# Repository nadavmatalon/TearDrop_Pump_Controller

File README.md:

#TearDrop Pump Controller

##Table of Contents

* [Screenshots](#screenshots)
* [About the Project](#about-the-project)
* [About the Pump Controller](#about-the-pump-controller)
* [License](#license)

##Screenshots

<table>
	<tr>
		<td align="center" width=25% >
			
		</td>
		<td align="center" width=25% >
			
		</td>
		<td align="center" width=25% >
			
		</td>
		<td align="center" width=25% >
			
		</td>
	</tr>
</table>

##About the Project
 
__TearDrop__ is a custom, open-frame, water-cooled scratch build I’ve been 
working on as part of the SnowCrash initiative.

The __SnowCrash__ initiative aims at designing and building end-to-end customized 
personal computers, addressing unique functional requirements – from developing 
the software control applications, to hardware configuration and case modding. 
As part of the initiative's research phase, the TearDrop customized computer 
prototype has been developed.

The underlying motivation for this specifc project was to research, design, 
prototype and finally create everything that's needed for a fully-customized 
desktop computer.

In this context, I’ve learned to program micro-controllers, design, prototype 
and build electronic circuit boards, make CNC cutting templates, interface with 
various kinds of hardware, write front-end applications, and lots more.

This project also helped me to become proficient in multiple software tools, including: 
[Google Sketchup](http://www.sketchup.com/), 
[Arduino IDE](http://www.arduino.cc/), [Processing 2.0](http://processing.org/), 
[CadSoft Eagle](http://www.cadsoftusa.com/download-eagle/freeware/), 
and [Inkscape](http://www.inkscape.org/en/).
 
The __project-log__ of this build (which I haven't had time to update recently, but 
does include loads of cool pictures :-), can be found 
at [bit-tech](http://forums.bit-tech.net/showthread.php?t=234218).

##About the Pump Controller

This repo contains the custom Pump Controller I’ve designed and built 
to control __TearDrop__’s dual-pump cooling system.

This repo contains the following files:

* __arduino__

    The source code for the ATmega328P that runs the Pump Controller 

    The file can can be directly accessed by clicking this link:

    * [Pump Controller](arduino/TearDrop_Pump_Controller/TearDrop_Pump_Controller.ino)

	The source code requires three supporting open-source [Arduino](http://www.arduino.cc/) libraries.

	For convenience, these libraries are inlcuded here in their own sub-folder.

	Credit goes to:

	[PinChangeInt](http://playground.arduino.cc/Main/PinChangeInt)

	[OneWire](https://github.com/ntruchsess/arduino-OneWire/tree/master)

	[WSWire](https://github.com/steamfire/WSWireLib)

* __eagle__

    This folder contains the complete hardware schematics & PCB design of the Pump Controller.

    __Please do not click on the files in this sub-folder as they are in foramts that 
    are incompatible with Github's hosting server__.

    However, the files can be downloaded and run as usual with [CadSoft](http://www.cadsoftusa.com/?language=en)'s 
    free version of [Eagle](http://www.cadsoftusa.com/download-eagle/freeware/).

* __parts__

	A speadsheet with all information about the parts used for building the Pump Controller.

	__The file in this sub-folder is also in a foramt that's incompatible with Github's hosting server__.

    However, it can be downloaded and run as usual with any spreadsheet editing software.

##  License

<p>Released under the <a href="http://www.opensource.org/licenses/MIT">MIT license</a>.</p>

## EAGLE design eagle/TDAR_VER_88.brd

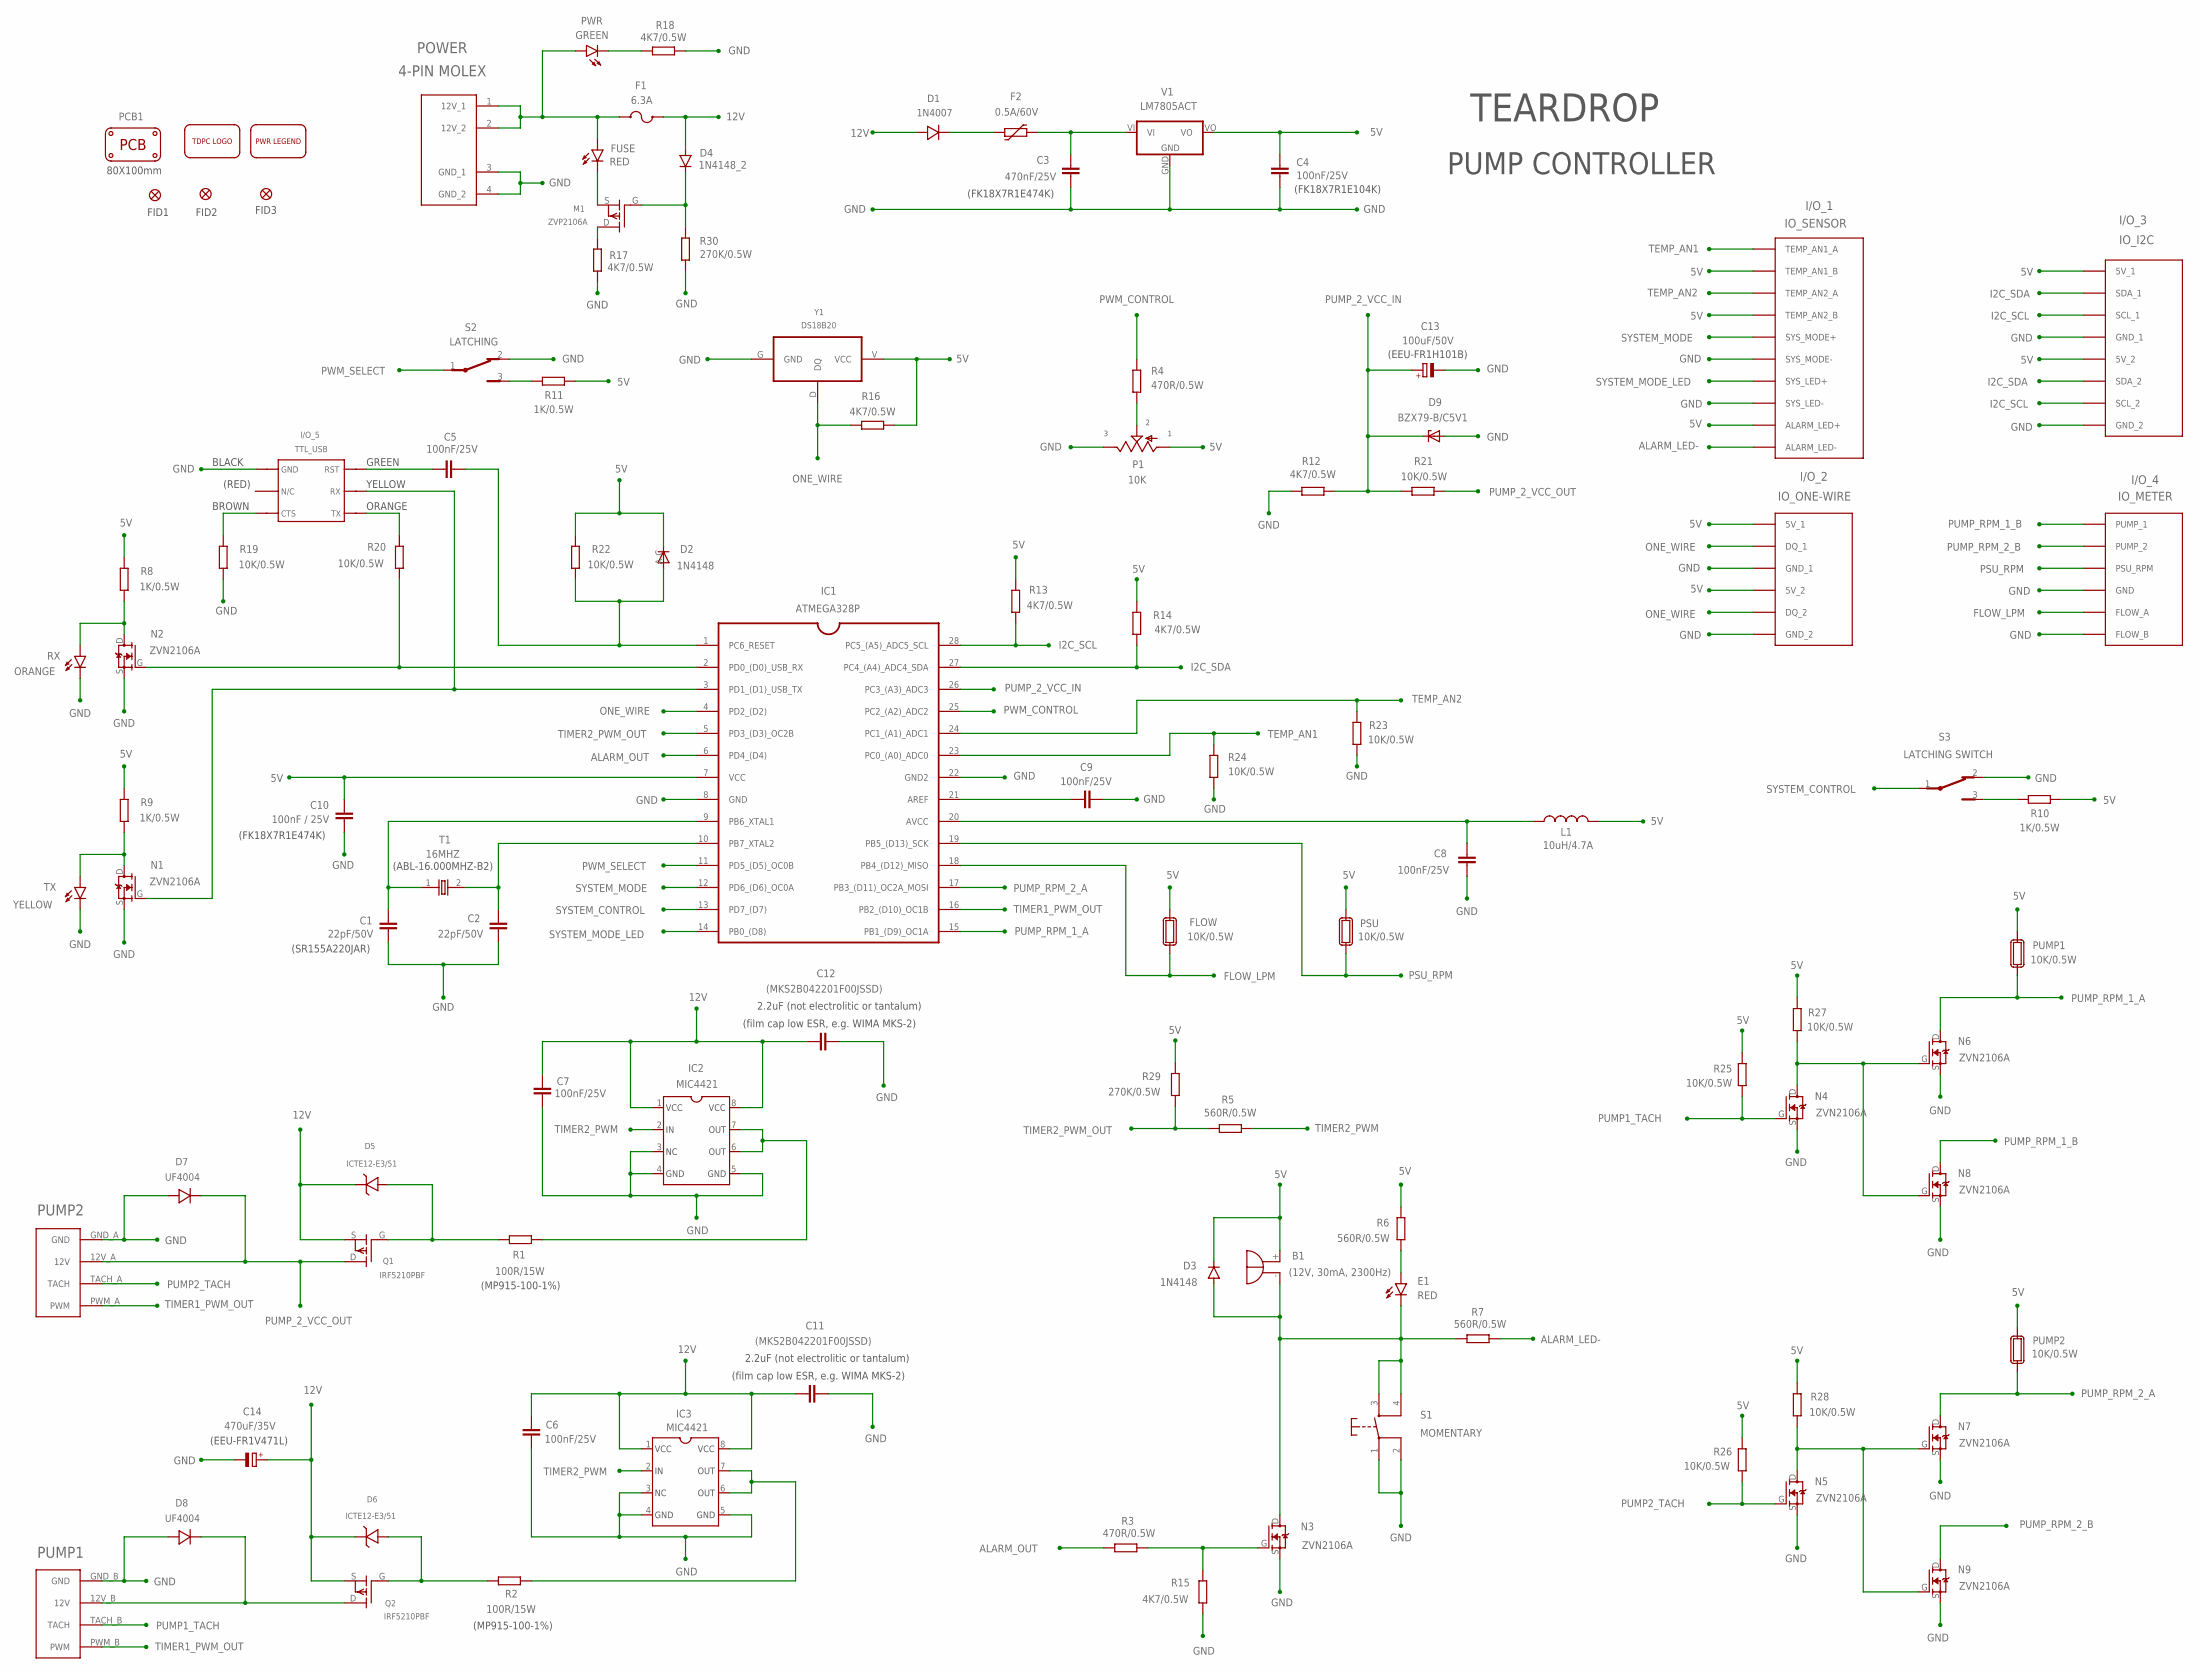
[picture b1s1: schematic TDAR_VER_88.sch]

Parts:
B1: (12V, 30mA, 2300Hz); F/TMB
C1: 22pF/50V; MLCC_CERAMIC_12
C2: 22pF/50V; MLCC_CERAMIC_11
C3: 470nF/25V; MLCC_CERAMIC_8
C4, C5, C6, C7: 100nF/25V; MLCC_CERAMIC
C8, C9: 100nF/25V; MLCC_CERAMIC_7
C10: 100nF / 25V; MLCC_CERAMIC_6
C11, C12: (MKS2B042201F00JSSD); WIMA_CAPACITOR
C13: 100uF/50V; E5-10,5
C14: 470uF/35V; E5-10,5
D1: 1N4007; UF4004
D2: 1N4148; DO35-7
D3: 1N4148
D4: 1N4148_2
D5, D6: ICTE12-E3/51; TVS_DIODE
D7, D8: UF4004; UF4004_2
D9: BZX79-B/C5V1; DO34Z7
E1: RED; LED_5_HORIZONTAL
F1: 6.3A; FUSE_GLASS
F2: 0.5A/60V; PTC
FID1, FID2, FID3: FIDUCIAL1X2; FIDUCIAL-1X2
FLOW: 10K/0.5W; RESISTOR_SOCKET_TOP
FUSE: RED; LED_1.8_LEFT
I/O_1: IO_SENSOR; IO_GENERAL_4
I/O_2: IO_ONE-WIRE; I0_ONE-WIRE
I/O_3: IO_I2C
I/O_4: IO_METER; IO_SENSOR_4
I/O_5: TTL_USB; TTL_USB_7
IC1: ATMEGA328P
IC2, IC3: MIC4421; TC4420
L1: 10uH/4.7A; IRF24
M1: ZVP2106A
N1, N2, N3, N4, N5, N6, N7, N8, N9: ZVN2106A
P1: 10K; POTENTIMETER_SQUARE
PCB1: 80X100mm; DP10080_V1
POWER: 4-PIN MOLEX; MOLEX_4PIN_2
PSU: 10K/0.5W; RESISTOR_SOCKET_TOP
PUMP1, PUMP2: 10K/0.5W; RESISTOR_SOCKET_TOP
PUMP_2: PUMP2; MOLEX_POWER_8_PIN_HORIZONTAL_2
PWR: GREEN; LED_1.8_LEFT
Q1, Q2: IRF5210PBF; IRF5210
R1, R2: 100R/15W; V234/12
R3, R4: 470R/0.5W; 0204/5
R5, R6, R7: 560R/0.5W; 0204/5
R8, R9, R10, R11: 1K/0.5W; 0204/5
R12, R13, R14, R15, R16, R17, R18: 4K7/0.5W; 0204/5
R19, R20, R21, R22, R23, R24, R25, R26, R27, R28: 10K/0.5W; 0204/5
R29, R30: 270K/0.5W; 0204/5
RX: ORANGE; LED_1.8_RIGHT
S1: MOMENTARY; MOM_SWITCH_6.0
S2: LATCHING; SLIDING_SWITCH_5
S3: LATCHING SWITCH; SLIDING_SWITCH_4
T1: 16MHZ; CRYSTAL_16MHZ
TX: YELLOW; LED_1.8_RIGHT
U$1: TDPC_LOGO
U$2: MOLEX_4PIN_LEGEND
V1: LM7805ACT; LM7805
Y1: DS18B20

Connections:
5V: B1.+, C4.2, C10.1, D2.C, D3.C, FLOW.1, I/O_1.5V_1 (TEMP_AN1_B), I/O_1.5V_2 (TEMP_AN2_B), I/O_1.ALARM_LED+, I/O_2.5V_1, I/O_2.5V_2, I/O_3.5V_1, I/O_3.5V_2, IC1.7 (VCC), L1.2, P1.1 (A), PSU.1, PUMP1.1, PUMP2.1, R6.1, R8.1, R9.1, R10.2, R11.2, R13.2, R14.1, R16.2, R22.1, R25.1, R26.1, R27.1, R28.2, R29.1, V1.VO, Y1.V (VCC)
12V: C6.2, C7.2, C11.1, C12.1, C14.+, D1.A, D4.A, D5.C, D6.C, F1.2, IC2.1, IC2.8, IC3.1, IC3.8, Q1.S, Q2.S
ALARM_LED-: I/O_1.ALARM_LED-, R7.2
ALARM_OUT: IC1.6 (PD4_(D4)), R3.2
CRYSTAL_A: C1.1, IC1.9 (PB6_XTAL1), T1.1
CRYSTAL_B: C2.1, IC1.10 (PB7_XTAL2), T1.2
D4: D5.A, Q1.G, R1.1
FLOW_LPM: FLOW.2, I/O_4.FLOW_A, IC1.18 (PB4_(D12)_MISO)
GND: C1.2, C2.2, C3.2, C4.1, C6.1, C7.1, C8.2, C9.2, C10.2, C11.2, C12.2, C13.-, C14.-, D7.A, D8.A, D9.A, I/O_1.SYSTEM_LED- (SYS_LED-), I/O_1.SYSTEM_MODE- (SYS_MODE-), I/O_2.GND_1, I/O_2.GND_2, I/O_3.GND_1, I/O_3.GND_2, I/O_4.FLOW_B, I/O_4.GND, I/O_5.GND, IC1.8 (GND), IC1.22 (GND2), IC2.3, IC2.4, IC2.5, IC3.3, IC3.4, IC3.5, N1.S, N2.S, N3.S, N4.S, N5.S, N6.S, N7.S, N8.S, N9.S, P1.3 (E), POWER.3 (GND_1), POWER.4 (GND_2), PUMP_2.GND_A (GND), PUMP_2.GND_B (GND), R12.1, R15.1, R17.2, R18.1, R19.2, R23.1, R24.2, R30.2, RX.K (C), S1.1, S1.2, S2.2, S3.2, TX.K (C), V1.GND, Y1.G (GND)
I2C_SCL: I/O_3.SCL_1, I/O_3.SCL_2, IC1.28 (PC5_(A5)_ADC5_SCL), R13.1
I2C_SDA: I/O_3.SDA_1, I/O_3.SDA_2, IC1.27 (PC4_(A4)_ADC4_SDA), R14.2
unnamed: R11.1, S2.3
unnamed: D4.C, M1.G, R30.1
unnamed: C8.1, IC1.20 (AVCC), L1.1
unnamed: PWR.K (C), R18.2
unnamed: P1.2 (S), R4.1
unnamed: IC2.6, IC2.7, R1.2
unnamed: D6.A, Q2.G, R2.1
unnamed: IC3.6, IC3.7, R2.2
unnamed: FUSE.K (C), M1.S
unnamed: N4.D, N6.G, N8.G, R27.2
unnamed: C9.1, IC1.21 (AREF)
unnamed: N3.G, R3.1, R15.2
unnamed: R10.1, S3.3
unnamed: D1.C, F2.1
unnamed: N1.D, R9.2, TX.A
unnamed: N2.D, R8.2, RX.A
unnamed: M1.D, R17.1
unnamed: E1.A, R6.2
unnamed: N5.D, N7.G, N9.G, R28.1
unnamed: B1.-, D3.A, E1.K (C), N3.D, R7.1, S1.3, S1.4
ONE_WIRE: I/O_2.DQ_1, I/O_2.DQ_2, IC1.4 (PD2_(D2)), R16.1, Y1.D (DQ)
POST_FUSE: C3.1, F2.2, V1.VI
PSU_RPM: I/O_4.PSU (PSU_RPM), IC1.19 (PB5_(D13)_SCK), PSU.2
PUMP1_TACH: N4.G, PUMP_2.TACH_B (TACH), R25.2
PUMP2_TACH: N5.G, PUMP_2.TACH_A (TACH), R26.2
PUMP_1_VCC_OUT: D8.C, PUMP_2.12V_B (12V), Q2.D
PUMP_2_VCC_IN: C13.+, D9.C, IC1.26 (PC3_(A3)_ADC3), R12.2, R21.1
PUMP_2_VCC_OUT: D7.C, PUMP_2.12V_A (12V), Q1.D, R21.2
PUMP_RPM_1_A: IC1.15 (PB1_(D9)_OC1A), N6.D, PUMP1.2
PUMP_RPM_1_B: I/O_4.PUMP_1, N8.D
PUMP_RPM_2_A: IC1.17 (PB3_(D11)_OC2A_MOSI), N7.D, PUMP2.2
PUMP_RPM_2_B: I/O_4.PUMP_2, N9.D
PWM_CONTROL: IC1.25 (PC2_(A2)_ADC2), R4.2
PWM_SELECT: IC1.11 (PD5_(D5)_OC0B), S2.1
PWR_IN: F1.1, FUSE.A, POWER.1 (12V_1), POWER.2 (12V_2), PWR.A
RESET: C5.1, D2.A, IC1.1 (PC6_RESET), R22.2
SYSTEM_CONTROL: IC1.13 (PD7_(D7)), S3.1
SYSTEM_MODE: I/O_1.SYSTEM_MODE+ (SYS_MODE+), IC1.12 (PD6_(D6)_OC0A)
SYSTEM_MODE_LED: I/O_1.SYSTEM_LED+ (SYS_LED+), IC1.14 (PB0_(D8))
TEMP_AN1: I/O_1.TEMP_AN1 (TEMP_AN1_A), IC1.23 (PC0_(A0)_ADC0), R24.1
TEMP_AN2: I/O_1.TEMP_AN2 (TEMP_AN2_A), IC1.24 (PC1_(A1)_ADC1), R23.2
TIMER1_PWM_OUT: IC1.16 (PB2_(D10)_OC1B), PUMP_2.PWM_A (PWM), PUMP_2.PWM_B (PWM)
TIMER2_PWM: IC2.2, IC3.2, R5.2
TIMER2_PWM_OUT: IC1.5 (PD3_(D3)_OC2B), R5.1, R29.2
USB_CTS: I/O_5.CTS, R19.1
USB_RESET_2: C5.2, I/O_5.RST
USB_RX: IC1.2 (PD0_(D0)_USB_RX), N2.G, R20.2
USB_RX_2: I/O_5.TX, R20.1
USB_TX: I/O_5.RX, IC1.3 (PD1_(D1)_USB_TX), N1.G

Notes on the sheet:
FID1
FID2
FID3
(film cap low ESR, e.g. WIMA MKS-2)
TEARDROP
GREEN
YELLOW
ORANGE
BROWN
BLACK
(RED)
2.2uF (not electrolitic or tantalum)
(FK18X7R1E104K)
(FK18X7R1E474K)
(SR155A220JAR)
(EEU-FR1V471L)
(EEU-FR1H101B)
(MP915-100-1%)
PUMP1
PUMP CONTROLLER
(ABL-16.000MHZ-B2)

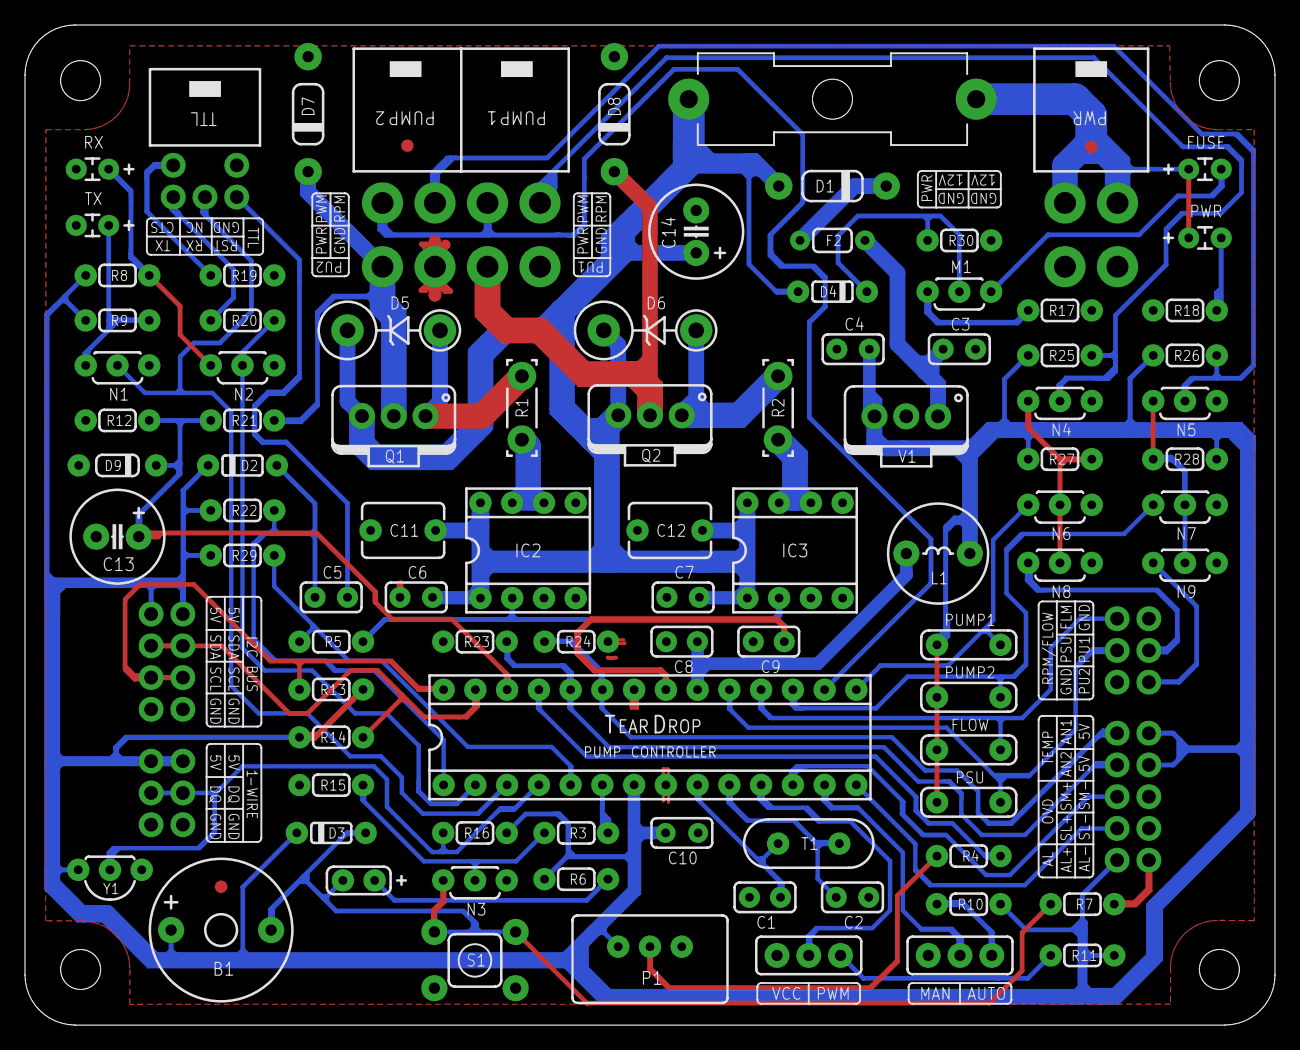
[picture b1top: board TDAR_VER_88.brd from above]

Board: 2 copper layers, 100.0 x 80.0 mm, 101 parts (0 on the bottom side), 60 nets.

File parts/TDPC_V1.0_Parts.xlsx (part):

| TEARDROP
 | NAME | TYPE | VALUE / RATING | PACKAGE / DIMENSIONS | NUMBER | MANUFACTURER | MPN | SOURCE | DATASHEET | ACTUAL | ACTUAL | MINIMUM | ACTUAL | MINIMUM | MINIMUM | ACTUAL | MINIMUM | MINIMUM | MINIMUM
 |  |  |  | (mm) | OF |  |  |  | LEAD | LEAD | LEAD | HOLE | HOLE | ANNULAR RING | PAD | PAD | HOLE | PAD | PAD
 |  |  |  |  | UNITS |  |  |  | DIAMETER | DIAMETER | DIAMETER | DIAMETER | DIAMETER | SIZE | DIAMETER | DIAMETER | DIAMETER | DIAMETER | DIAMETER
 |  |  |  |  |  |  |  |  | (mm) | (wide side) | (narrow side) | (mm) | (mm) | (mm) | (mm) | (mm) | CHECK | CHECK (1) | CHECK (2)
 | PWR, PUMP1, PUMP2 | 4P (2x2) POWER SOCKET (FEMALE) | 10A | KK, HORIZONTAL | 3 | MOLEX | MB-4PIN-SB | modDIY (MB-4PIN-SB) | ─ | 1.2 | 1.2 | 1.454 | 1.75 | 0.2 | 2.25 | 3.3 | 1.35 | 0.14999999999999991 | 1.0499999999999998
 | PWR, PUMP1, PUMP2 | 4P (2x2) POWER CONNECTOR (MALE) | 10A | KK, HORIZONTAL | 3 | MOLEX | MB-4PIN-F | modDIY (MB-4PIN-F) | ─ | ─ | ─ | ─ | ─ | ─ | ─ | ─ | ─ | ─ | ─
 | USB-TTL | 6P (2x3) SOCKET (FEMALE) | RIGHT ANGLE, 2.54 |  | 1 | MOLEX | 90130-3206 | eBay (350819406809) |  |  |  | 0.254 |  | 0.2 | 0.5 | 1.7 | -0.4 | 1.7 | 1.2
 | USB-TTL | 6P (2x3) CONNECTOR (MALE) | ─ | ─ | 1 | MOLEX | 90142-0006 | eBay (111189947049) | ─ | ─ | ─ | ─ | ─ | ─ | ─ | ─ | ─ | ─ | ─
 | USB-TTL | CONNECTOR CRIMPS | ─ | ─ | 6 | MOLEX | 90119-2120 | eBay (111189965216) | ─ | ─ | ─ | ─ | ─ | ─ | ─ | ─ | ─ | ─ | ─
 | I/O | RIGHT-ANGLE MALE HEADERS | 2x3, 2x4, 2x5 | DUAL ROW, 2.54 | 3 | UNKOWN | UNKNOWN | eBay (321027689319) | ─ | 0.7 | 0.7 | 0.95399999999999996 | 1.1000000000000001 | 0.2 | 1.6 | 2 | 0.70000000000000007 | 1.9999999999999796E-2 | 0.39999999999999991
 | IC1 | ATMEGA328P | ─ | DIP-28 | 1 | ATMEL | ATMEGA328P | eBay(281158389853) | ─ | ─ | ─ | ─ | ─ | ─ | ─ | ─ | ─ | ─ | ─
 | (IC1) | DIL-28 SOCKET | ─ | 35.6x10, 2.54 | 1 | UNKNOWN | UNKNOWN | eBay(181062492231) | 0.5 | 0.5 | 0.5 | 0.754 | 0.7 | 0.2 | 1.2000000000000002 | 1.8 | 0.29999999999999993 | 0.54 | 0.60000000000000009
 | IC2, IC3 | MIC4421 (MOFSET DRIVER) | 9A | DIP-8 | 2 | MICREL | MIC4421YN | Mouser (998-MIC4421YN) | ─ | ─ | ─ | ─ | ─ | ─ | ─ | ─ | ─ | ─ | ─
 | [IC2, IC3] | [MCP1406 (IMPROVEMENT OF TC4429)] | [6A] | [DIP-8] | [2] | MICROCHIP | MCP1406-E/P | Mouser (579-MCP1406-E/P) | ─ | ─ | ─ | ─ | ─ | ─ | ─ | ─ | ─ | ─ | ─
 | (IC2, IC3) | DIL-8 SOCKET | 3A | 10.1x10.2 | 2 | MILL-MAX | 110-44-308-41-001000 | Mouser (575-144308) | 0.5 | 0.5 | 0.5 | 0.754 | 0.7 | 0.2 | 1.2000000000000002 | 1.8 | 0.29999999999999993 | 0.54 | 0.60000000000000009
 |  |  |  |  |  |  |  | Farnell (1351428)
 | [IC2, IC3] | [DIL-8 SOCKET] | [3A] | [10x10] | [2] | TE Connectivity / AMP | 808-AG11D-ES-LF | Mouser (571-4-1571552-3) | 0.5 | 0.5 | 0.5 | 0.754 | 0.7 | 0.2 | 1.2000000000000002 | 1.8 | 0.29999999999999993 | 0.54 | 0.60000000000000009
 | Y1 | DS18B20 (DIGITAL TEMPERATURE SENSOR) | ─ | TO-92 | 1 | DALLAS | DS18B20 | eBay (301049284143) | 0.5 | 0.5 | 0.5 | 0.754 | 0.7 | 0.2 | 1.2000000000000002 | 1.8 | 0.29999999999999993 | 0.54 | 0.60000000000000009
 | V1 | LM7805 (VOLTAGE REGULATOR) | 5V | TO-220 | 1 | FAIRCHILD | LM7805ACT | Mouser (512-LM7805ACT) | Narrow: 0.64 | 0.86 | 0.45 | 1.1139999999999999 | 1.1000000000000001 | 0.2 | 1.6 | 2.1 | 0.70000000000000007 | 0.11999999999999988 | 0.5
 |  |  |  |  |  |  |  |  | Wide: 1.52
 | [V1] | [LM7805 (VOLTAGE REGULATOR)] | [5V] | [TO-220] | [1] | ON SEMICONDUCTOR | MC33269T-5.0G | Mouser (863-MC33269T-5.0G) | Narrow: 0.64 | 0.86 | 0.45 | 1.1139999999999999 | 1.2 | 0.2 | 1.7000000000000002 | 2.1 | 0.79999999999999993 | -6.0000000000000053E-2 | 0.40000000000000013
 |  |  |  |  |  |  |  |  | Wide: 1.52
 | F1 | FAST-BLOW GLASS FUSE | 6.3A | 8x20MM | 1 | UKNOWN | UNKWNON | UNKNOWN | ─ | ─ | ─ | ─ | ─ | ─ | ─ | ─ | ─ | ─ | ─
 | (F1) | FUSE HOLDER | 10A / 250V | 22.5x9.6mm | 1 | Schurter | 0031.8211 | Mouser (693-0031.8201) | 1.3 | 1.2 | 0.46 | 1.454 | 1.45 | 0.2 | 1.9500000000000002 | 3.3 | 1.0499999999999998 | 0.69 | 1.3499999999999999
 | F2 | PTC (RESETTABLE FUSE) | 0.5A / 60V | 6.8x1.9, 5.1 | 1 | BOURNS | MF-R050 | Mouser (652-MFR050) | 0.5 | 0.55000000000000004 | 0.5 | 0.80400000000000005 | 0.7 | 0.2 | 1.2000000000000002 | 1.6 | 0.29999999999999993 | 0.34000000000000008 | 0.40000000000000013
 | L1 | INDUCTOR | 10uH / 4A7 | 8.7x12.3, 5.08 | 1 | Wurth Electronics | 7447452100 | Mouser (710-7447452100) | 0.7 | 0.65 | 0.7 | 0.90400000000000003 | 0.9 | 0.2 | 1.4000000000000001 | 2.1 | 0.5 | 0.48 | 0.70000000000000018
 | C1, C2 | CAPACITOR (MLCC) | 22pF / 50V | 3.8x2, 2.6 | 2 | AVX | SR155A220JAR | Mouser (581-SR155A220JAR) | 0.5 | 0.5 | 0.5 | 0.754 | 0.7 | 0.2 | 1.2000000000000002 | 1.7 | 0.29999999999999993 | 0.43999999999999995 | 0.5
 | C3 | CAPACITOR (MLCC) | 470nF / 25V | 4x2.5, 3 | 1 | TDK | FK18X7R1E474K | Mouser (810-FK18X7R1E474K) | 0.5 | 0.55000000000000004 | 0.55000000000000004 | 0.80400000000000005 | 0.7 | 0.2 | 1.2000000000000002 | 1.7 | 0.29999999999999993 | 0.43999999999999995 | 0.5
 | C4 - C10 | CAPACITOR (MLCC) | 100nF / 100V | 4.3x2.9, 2.6 | 7 | NOT KNOWN | NOT KNOWN | eBay (290933035294) | 0.5 | 0.5 | 0.5 | 0.754 | 0.7 | 0.2 | 1.2000000000000002 | 1.7 | 0.29999999999999993 | 0.43999999999999995 | 0.5
 | [C4 - C10] | [CAPACITOR (MLCC)] | [100nF / 25V] | [4x2.5, 3] | [7] | [TDK] | [FK18X7R1E104K] | [Mouser (810-FK18X7R1E104K)] | 0.5 | 0.5 | 0.5 | 0.754 | 0.7 | 0.2 | 1.2000000000000002 | 1.8 | 0.29999999999999993 | 0.54 | 0.60000000000000009
 | C11, C12 | WIMA CAPACITOR (5%) | 2.2uF / 50V | 5x7.2, 5.2 | 2 | WIMA | MKS2B042201F00JSSD | Mouser (505-MKS22.2/50/5) | 0.5 | 0.5 | 0.5 | 0.754 | 0.7 | 0.2 | 1.2000000000000002 | 1.8 | 0.29999999999999993 | 0.54 | 0.60000000000000009
 | [C11, C12] | [WIMA CAPACITOR (10%)] | [2.2uF / 50V] | [5x7.2, 5] | [2] | [WIMA] | [MKS2B042201F00KSSD] | [Mouser (505-MKS22.2/50/10 )] |  |  |  | 0.254 |  |  | 0.1 |  | -0.4 | 0 | -0.5
 | [C11, C12] | [WIMA CAPACITOR (10%)] | [4.7uF / 50V] | [7.2x7.2, 5] | [2] | [WIMA] | [MKS2B044701K00KSSD] | [Mouser (505-MKS2-4.7/50/10)] |  |  |  | 0.254 |  |  | 0.1 |  | -0.4 | 0 | -0.5
 | [C11, C12] | [WIMA CAPACITOR (5%)] | [1uF / 63V] | [5x7.2, 5] | [2] | WIMA | [MKS2C041001F00JS] | [Mouser (505-MKS21.0/63/5)] |  |  |  | 0.254 |  |  | 0.1 |  | -0.4 | 0 | -0.5
 | [C11, C12] | [WIMA CAPACITOR (5%)] | [1uF / 63V] | [5x7.2, 5] | [2] | [WIMA] | [MKS2-1/63/5T] | [Mouser (505-MKS21/63/5T)] |  |  |  | 0.254 |  |  | 0.1 |  | -0.4 | 0 | -0.5
 | C13 | CAPACITOR (ELECTROLYTIC) | 100uF / 50V | 8x12.2, 5 | 1 | PANASONIC | EEU-FR1H101B | Mouser (667-EEU-FR1H101B) | 0.6 | 0.6 | 0.6 | 0.85399999999999998 | 0.9 | 0.2 | 1.4000000000000001 | 2.1 | 0.5 | 0.48 | 0.70000000000000018
 | C14 | CAPACITOR (ELECTROLITIC) | 470uF / 35V | 8.3x21.6, 3.5 | 1 | PANASONIC | EEU-FR1V471L | Mouser 667-EEU-FR1V471L | 0.6 | 0.6 | 0.6 | 0.85399999999999998 | 0.9 | 0.2 | 1.4000000000000001 | 2.1 | 0.5 | 0.48 | 0.70000000000000018
 | Q1, Q2 | IRF5210 (P-CHANNEL MOSFET) | 30V / 50A | TO-220 | 2 | INTERNATIONAL RECIFIER | IRF5210PBF | Mouser (942-IRF5210PBF) | Narrow: 0.64 | 0.86 | 0.45 | 1.1139999999999999 | 1.1000000000000001 | 0.2 | 1.6 | 2.1 | 0.70000000000000007 | 0.11999999999999988 | 0.5
 |  |  |  |  |  |  |  |  | Wide: 1.52
 | (Q1, Q2, V1) | MOSFET / VOLTAGE REGULATOR HEATSINK (TO-220) | 32C/W | 6.35x13.3 | 3 | AAVID THERMALLOY | 577002B00000G | Mouser (532-577002B00) | ─ | ─ | ─ | ─ | ─ | ─ | ─ | ─ | ─ | ─ | ─
 | N1 - N9 | ZVN2106A (N-CHANNEL MOSFET) | 0.2A / 60V | TO-92 | 9 | FAIRCHILD | ZVN2106A | Mouser (522-ZVN2106A) | 0.5 | 0.5 | 0.5 | 0.754 | 0.7 | 0.2 | 1.2000000000000002 | 1.8 | 0.29999999999999993 | 0.54 | 0.60000000000000009
 | M1 | ZVP2106A (P-CHANNEL MOSFET) | 0.2A / 60V | 2.3x4.6 | 1 | DIODES INC | ZVP2106A | Mouser (522-ZVP2106A) | 0.5 | 0.5 | 0.5 | 0.754 | 0.7 | 0.2 | 1.2000000000000002 | 1.8 | 0.29999999999999993 | 0.54 | 0.60000000000000009
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
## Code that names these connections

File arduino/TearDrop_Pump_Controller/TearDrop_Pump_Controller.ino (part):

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
// PUMP CONTROLLER (COM5)

// PIN_D2  (PIN 4)   -  ONE_WIRE
// PIN_D3  (PIN 5)   -  FREQ_VCC (TIMER2)
// PIN_D4  (PIN 6)   -  ALARM_OUT
// PIN_D5  (PIN 11)  -  SYSTEM_MODE (VCC/PWM)
// PIN_D6  (PIN 12)  -  SYSTEM_CONTROL_1 (OVD_OFF/OVD_ON)
// PIN_D7  (PIN 13)  -  SYSTEM_CONTROL_2 (MAN/AUTO)
// PIN_D8  (PIN 14)  -  SYSTEM_CONTROL_LED
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// PIN_D10 (PIN 16)  -  FREQ_PWM (TIMER1)
// PIN_D11 (PIN 17)  -  PUMP_RPM_2
// PIN_D12 (PIN 18)  -  PUMP_FLOW
// PIN_D13 (PIN 19)  -  PSU_RPM
// PIN_A0  (PIN 23)  -  TEMP_AN1
// PIN_A1  (PIN 24)  -  TEMP_AN2
// PIN_A2  (PIN 25)  -  PUMP_CONTROL (RAW_POT)
// PIN_A3  (PIN 26)  -  PUMP_VCC
// PIN_A4  (PIN 27)  -  I2C_SDA
// PIN_A5  (PIN 28)  -  I2C_SCL

// http://playground.arduino.cc/Main/PinChangeInt
// http://code.google.com/p/arduino-pinchangeint/
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// const boolean PSU_ALARM = true;		// PSU_ALARM_ON


const byte PIN_D2 = 2;				// ONE_WIRE
const byte PIN_D3 = 3;				// FREQ_VCC (TIMER2)
const byte PIN_D4 = 4;				// ALARM_OUT
const byte PIN_D5 = 5;				// SYSTEM_MODE (VCC/PWM)
const byte PIN_D6 = 6;				// SYSTEM_CONTROL_1 (OVD_ON/OVD_OFF)
const byte PIN_D7 = 7;				// SYSTEM_CONTROL_2 (MAN/AUTO)
const byte PIN_D8 = 8;				// SYSTEM_CONTROL_LED
const byte PIN_D9 = 9;				// PUMP_RPM_1
const byte PIN_D10 = 10;			// FREQ_PWM (TIMER1)
const byte PIN_D11 = 11;			// PUMP_RPM_2
const byte PIN_D12 = 12;			// FLOW_LPM
const byte PIN_D13 = 13;			// PSU_RPM
const byte PIN_A0 = A0;				// TEMP_AN1
const byte PIN_A1 = A1;				// TEMP_AN2
const byte PIN_A2 = A2;				// PUMP_CONTROL (RAW_POT)
const byte PIN_A3 = A3;				// PUMP_VCC

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const unsigned int AN_TEMP_THRESHOLD = 500;						// defines Alarm activation higher threshold for Analog Temp sensors (in Celsuis)
const unsigned int IC_TEMP_THRESHOLD = 500;						// defines Alarm activation higher threshold for IC (ATmega328p) Internal sensor (in Celsuis)

const float TEMP_OFFSET_A0 = 1.00;							// TEMP_AN1 - calibration function: higher OFFSET precentage => lower temperature readings
const float TEMP_OFFSET_A1 = 1.00;							// TEMP_AN2 - calibration function: higher OFFSET precentage => lower temperature readings

const unsigned int TEMP_RESISTOR_A0 = 10000;	// TEMP_AN1_RESISTOR			// TEMP_AN1 - resistor value on PIN_A0 (in Ohms)
const unsigned int TEMP_RESISTOR_A1 = 10000;	// TEMP_AN2_RESISTOR			// TEMP_AN2 - resistor value on PIN_A1 (in Ohms)

const unsigned int FLOW_DIAMETER_OFFSET = 307;						// set for 10mm tube diameter 

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const unsigned int PC_SYSTEM_CONTROL_2 = 1003;	// SYSTEM_CONTROL_2(MAN/AUTO)		// PC_SYSTEM_CONTROL_2 processing update command
const unsigned int PC_VCC_PUMP = 1004;		// VCC_PUMP				// PC_VCC_PUM processing update command
const unsigned int PC_VCC_ICP = 1005;		// VCC_ICP				// PC_VCC_ICP processing update command
const unsigned int PC_SYSTEM_MODE = 1006;	// SYSTEM_MODE (VCC/PWM)		// PC_SYSTEM_MODE processing update command
const unsigned int PC_PUMP_RPM_1 = 1007;	// PUMP_RPM_1				// PC_PUMP_RPM_1 processing update command
const unsigned int PC_PUMP_RPM_2 = 1008;	// PUMP_RPM_2				// PC_PUMP_RPM_2 processing update command
const unsigned int PC_PSU_RPM = 1009;		// PSU_RPM				// PC_PSU_RPM processing update command
const unsigned int PC_PUMP_FLOW = 1010;		// PUMP_FLOW				// PC_PUMP_FLOW processing update command
const unsigned int PC_DUTY_CYCLE_PER = 1011;	// PUMP_DUTY_CYCLE_PER			// PC_DUTY_CYCLE_PER processing update command
const unsigned int PC_TEMP_AN1 = 1012;		// TEMP_AN1				// PC_TEMP_AN1 processing update command
const unsigned int PC_TEMP_AN2 = 1013;		// TEMP_AN2 				// PC_TEMP_AN2 processing update command
const unsigned int PC_TEMP_DGP = 1014;		// TEMP_DGP (TEMP_OW_1)			// PC_TEMP_DGP processing update command
const unsigned int PC_TEMP_ICP = 1015;		// TEMP_ICP 				// PC_TEMP_ICP processing update command
const unsigned int PC_FREQ_VCC = 1016;		// FREQ_VCC				// PC_FREQ_VCC processing update command
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const unsigned int FC_FAN_RPM_5 = 2013;		// FAN_RPM_5				// FC_FAN_RPM_5 processing update command
const unsigned int FC_FAN_RPM_6 = 2014;		// FAN_RPM_6				// FC_FAN_RPM_6 processing update command
const unsigned int FC_DUTY_CYCLE_PER_2 = 2015;	// DUTY_CYCLE_PER_2			// FC_DUTY_CYCLE_PER_2 processing update command
const unsigned int FC_TEMP_AN1 = 2016;		// TEMP_AN1				// FC_TEMP_AN3 processing update command
const unsigned int FC_TEMP_AN2 = 2017;		// TEMP_AN2				// FC_TEMP_AN4 processing update command
const unsigned int FC_TEMP_DGF = 2018;		// TEMP_DGF (TEMP_OW_1)			// FC_TEMP_DG processing update command
const unsigned int FC_TEMP_ICF = 2019;		// TEMP_ICF (TOP)			// FC_TEMP_IC processing update command
const unsigned int FC_FREQ_VCC_1 = 2020;	// FREQ_VCC_1				// FC_FREQ_VCC_1 processing update command
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
boolean system_control_2 = true;		// MAN/AUTO				// stores state of swtich on PIN_D7 (MAN/AUTO)

boolean system_mode = true;			// VCC/PWM				// stores state of swtich on PIN_D5 (VCC/PWM)

unsigned int pump_control = 880;		// PUMP_CONTROL (RAW_POT)		// PUMP_CONTROL - raw pot reading for duty cycle calculation

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
unsigned int pump_rpm_1 = 0;			// PUMP_RPM_1				// stores rpm reading on PIN_D9
unsigned int pump_rpm_2 = 0;			// PUMP_RPM_2				// stores rpm reading on PIN_D11
unsigned int psu_rpm = 0;			// PSU_RPM				// stores rpm reading on PIN_D13

unsigned int pump_flow = 0;			// PUMP_FLOW				// stores current flow rate (in LPM) on PIN_D12 (multiplied by 100)							

unsigned int temp_AN1 = 0;			// TEMP_AN1				// stores TEMP_AN1 readings (PIN_A0) 
unsigned int temp_AN2 = 0;			// TEMP_AN2				// stores TEMP_AN2 readings (PIN_A1)

unsigned int top_temp_AN = 550;			// TOP_TEMP_AN				// stores the current top temperature between temp_AN1 & temp_AN_2

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void setup() {

	DDRD |= (1 << DDD3); 				// VCC_DRIVE (TIMER2)		// VCC_DRIVE (TIMER2) - pinMode(PIN_D3, OUTPUT)
	DDRD |= (1 << DDD4); PORTD &= ~(1 << PORTD4);	// ALARM_OUT			// ALARM_OUT - pinMode(PIN_D4, OUTPUT); digitalWrite(PIN_D4, LOW)
	DDRD &= ~(1 << DDD5); 				// SYSTEM_MODE (VCC/PWM)	// SYSTEM_MODE (VCC/PWM) - pinMode(PIN_D5, INPUT)
	DDRD &= ~(1 << DDD6); PORTD |= (1 << PORTD6);	// SYSTEM_CONTROL_1 (OVD)	// SYSTEM_CONTROL_1 (OVD) - pinMode(PIN_D6, INPUT_PULLUP)
	DDRD &= ~(1 << DDD7); 				// SYSTEM_CONTROL_2 (MAN/AUTO)	// SYSTEM_CONTROL_2 (MAN/AUTO) - pinMode(PIN_D7, INPUT)
	DDRB |= (1 << DDB0); PORTB &= ~(1 << PORTB0); 	// SYSTEM_CONTROL_LED		// SYSTEM_CONTROL_LED - pinMode(PIN_D8, OUTPUT); digitalWrite(PIN_D8, LOW)
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	DDRB |= (1 << DDB2); 				// PWM_DRIVE (TIMER1)		// PWM_DRIVE (TIMER1) - pinMode(PIN_D10, OUTPUT)
	DDRB &= ~(1 << DDB3);				// PUMP_RPM_2 (NO_PULLUP)	// PUMP_RPM_2 - pinMode(PIN_D11, INPUT)
//	DDRB &= ~(1 << DDB3); PORTB |= (1 << PORTB3);	// PUMP_RPM_2 (PULLUP)		// PUMP_RPM_2 - pinMode(PIN_D11, INPUT_PULLUP)
	DDRB &= ~(1 << DDB4); 				// FLOW_LPM (NO_PULLUP)		// FLOW_LPM - pinMode(PIN_D12, INPUT)
//	DDRB &= ~(1 << DDB4); PORTB |= (1 << PORTB4);	// FLOW_LEP (PULLUP)		// FLOW_LPM - pinMode(PIN_D12, INPUT_PULLUP)
	DDRB &= ~(1 << DDB5); 				// PSU_RPM (NO_PULLUP)		// PSU_RPM - pinMode(PIN_D13, INPUT)
//	DDRB &= ~(1 << DDB5); PORTB |= (1 << PORTB5);	// PSU_RPM (PULLUP)		// PSU_RPM - pinMode(PIN_D13, INPUT_PULLUP)
	DDRC &= ~(1 << DDC0);				// TEMP_AN1			// TEMP_AN1 - pinMode(PIN_A0, INPUT)
	DDRC &= ~(1 << DDC1);				// TEMP_AN2			// TEMP_AN2 - pinMode(PIN_A1, INPUT)
	DDRC &= ~(1 << DDC2);				// PUMP_CONTROL			// PUMP_CONTROL - pinMode(PIN_A2, INPUT)
	DDRC &= ~(1 << DDC3);				// VCC_PUMP			// VCC_PUMP - pinMode(PIN_A3, INPUT)

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
		pump_rpm_2 = read_RPM(PIN_D11);						// updates rpm reading on PIN_D11

		temp_AN1 = update_Temp_AN(PIN_A0);		// TEMP_AN1		// reads analog temperature sensor on PIN_A0

		psu_rpm = read_RPM(PIN_D13);						// updates rpm reading on PIN_D13

		pump_flow = read_Flow(PIN_D12);						// updates flow meter reading on PIN_D12 (multiplied by 100)

		temp_AN2 = update_Temp_AN(PIN_A1);		// TEMP_AN2		// reads analog temperature sensor on PIN_A1

		top_temp_AN = update_Top_Temp_AN();		// TEMP_AN_TOP

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
	system_control_2 = bitRead(PIND, 7);			// MAN/AUTO						// digitalRead(PIN_D7) (0 => MAN; 1 => AUTO)

	system_mode = bitRead(PIND, 5);				// VCC/PWM						// digitalRead(PIN_D5) (0 => VCC; 1 => PWM)

	if ((currentStartupCount >= KICKSTART_INTERVAL) && (!system_control_1)) { 	// OVD_OFF			// SYSTEM_CONTROL_1 => OVD_OFF

		if (bitRead(PINB, 0)) PORTB &= ~(1 << PORTB0);				// OVD_LED_OFF			// turns off SYSTEM_MODE_LED (PIN_D8)

		if (!system_control_2) {			// MANUAL						// SYSTEM_CONTROL => MANUAL

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				currentBurp_D11 = 0;					// resets rpm count on PIN_D11 to zero
			sei();								// enables global interrupts
			break;
		case (PIN_D13): 							// PSU_RPM
		     	previous_rpm = psu_rpm;    	
			cli();								// disables global interrupts
				current_rpm = currentBurp_D13;				// obtains current rpm count from interrupt routine
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	
	switch (temp_pin) {												// sets offset coefficient for selected pin

		case (PIN_A0):						// TEMP_AN1 

			current_an_data = read_ADC(ADC_A0);								// calculates temperature on selected pin

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			break;


		case (PIN_A1): 						// TEMP_AN2

			current_an_data = read_ADC(ADC_A1);								// calculates temperature on selected pin
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
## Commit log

2014-08-25 uploaded TearDrop Pump Controller Files
2014-08-25 updated README file

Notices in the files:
parts and their libraries:
SparkFun-Aesthetics: Licensing: CC v3.0 Share-Alike You are welcome to use this library for commercial purposes.
